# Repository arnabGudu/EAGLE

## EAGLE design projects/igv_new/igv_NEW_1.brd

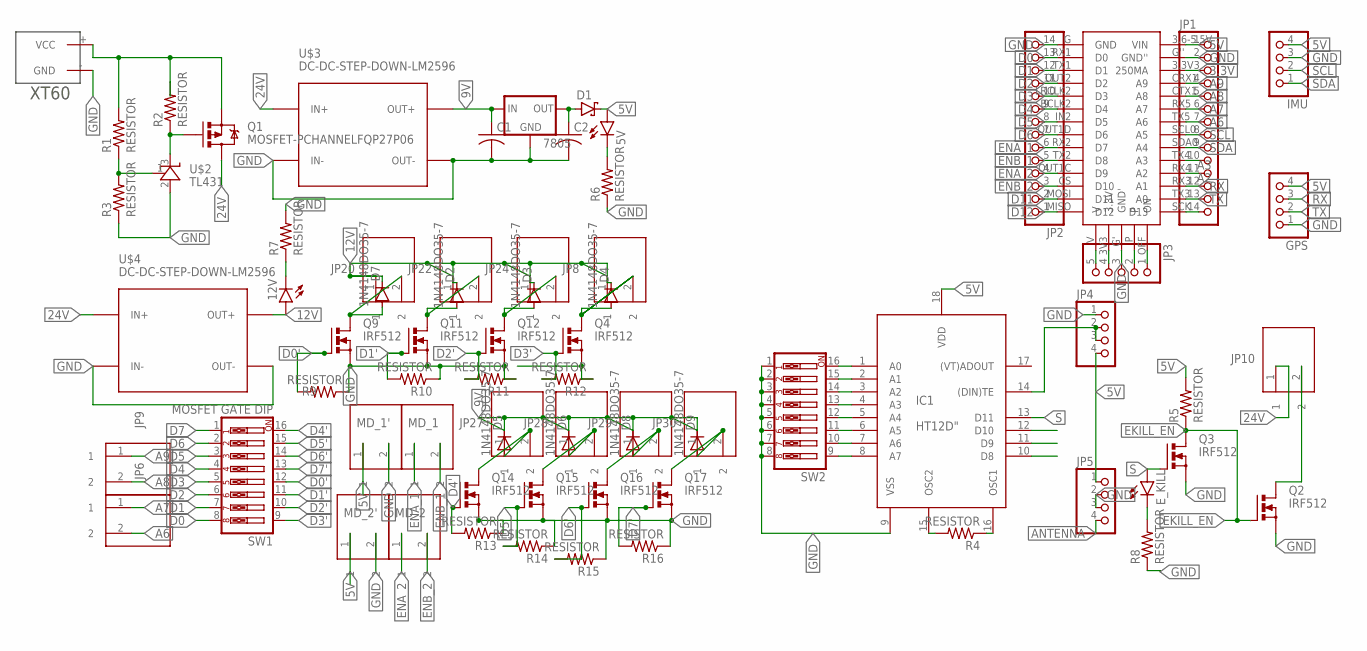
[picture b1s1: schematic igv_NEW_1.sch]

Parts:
5V, 12V: LED3MM
7805: 78XXS
C1, C2: C-US025-025X050; C025-025X050
D1: SCHOTTKY-DIODECB417-15; CB417-15
D2, D3, D4, D5, D6, D7, D8, D9: 1N4148DO35-7; DO35-7
E_KILL: LED3MM
GPS: ROTARY_ENCODER; 1X04
IC1: HT12D"; 18-DIP-A
IMU: ROTARY_ENCODER; 1X04
JP1, JP2: PINHD-1X14; 1X14
JP3: PINHD-1X5; 1X05
JP4, JP5: PINHD-1X4; 1X04
JP6, JP8, JP9, JP10, JP20, JP22, JP24, JP27, JP28, JP29, JP30: O/P_HEADER
MD_1, MD_1', MD_2, MD_2': O/P_HEADER
Q1: MOSFET-PCHANNELFQP27P06; TO220V
Q2, Q3, Q4, Q9, Q11, Q12, Q14, Q15, Q16, Q17: IRF512; TO220BV
R1, R2, R3, R4, R5, R6, R7, R8, R9, R10, R11, R12, R13, R14, R15, R16: RESISTOR; 0207/10
SW1: MOSFET GATE DIP; EDG-08
SW2: SW_DIP-8; EDG-08
U$1: TEENSY_4.0
U$2: TL431; TO-92
U$3, U$4: DC-DC-STEP-DOWN-LM2596
U$5: XT60

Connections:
3.3V: JP1.3, U$1.3.3V (250MA)
5V: 5V.A, D1.C, GPS.4, IC1.18 (VDD), IMU.4, JP1.1, JP4.4, JP5.1, MD_1'.1, MD_2'.1, R5.P$2 (2), U$1.3.6-5.5V (VIN)
9V: 7805.IN, C1.1, D5.C, D6.C, D8.C, D9.C, JP27.1, JP28.1, JP29.1, JP30.1, U$3.OUT+
12V: 12V.A, D2.C, D3.C, D4.C, D7.C, JP8.1, JP20.1, JP22.1, JP24.1, U$4.OUT+
24V: JP10.1, Q1.2 (D), U$3.IN+, U$4.IN+
A2: JP1.11, U$1.RX4 (A2)
A3: JP1.10, U$1.TX4 (A3)
A6: JP1.7, JP6.2, U$1.TX5 (A6)
A7: JP1.6, JP6.1, U$1.RX5 (A7)
A8: JP1.5, JP9.2, U$1.CTX1 (A8)
A9: JP1.4, JP9.1, U$1.CRX1 (A9)
ANTENNA: JP5.4
D0: JP2.13, SW1.8, U$1.RX1 (D0)
D0': Q9.G, R9.P$2 (2), SW1.12
D1: JP2.12, SW1.7, U$1.TX1 (D1)
D1': Q11.G, R10.P$2 (2), SW1.11
D2: JP2.11, SW1.6, U$1.OUT2 (D2)
D2': Q12.G, R11.P$2 (2), SW1.10
D3: JP2.10, SW1.5, U$1.LRCLK2 (D3)
D3': Q4.G, R12.P$2 (2), SW1.9
D4: JP2.9, SW1.4, U$1.BCLK2 (D4)
D4': Q14.G, R13.P$2 (2), SW1.16
D5: JP2.8, SW1.3, U$1.IN2 (D5)
D5': Q15.G, R14.P$2 (2), SW1.15
D6: JP2.7, SW1.2, U$1.OUT1D (D6)
D6': Q16.G, R15.P$2 (2), SW1.14
D7: SW1.1
D7': Q17.G, R16.P$2 (2), SW1.13
D11: JP2.2, U$1.MOSI (D11)
D12: JP2.1, U$1.MISO (D12)
EKILL_EN: Q2.G, Q3.D, R5.P$1 (1)
ENA_1: JP2.6, MD_1.1, U$1.RX2 (D7)
ENA_2: JP2.4, MD_2.1, U$1.OUT1C (D9)
ENB_1: JP2.5, MD_1.2, U$1.TX2 (D8)
ENB_2: JP2.3, MD_2.2, U$1.CS (D10)
GND: 7805.GND, C1.2, C2.2, GPS.1, IC1.9 (VSS), IMU.3, JP1.2, JP2.14, JP3.3, JP4.1, JP5.2, JP5.3, MD_1'.2, MD_2'.2, Q2.S, Q3.S, Q9.S, Q11.S, Q12.S, Q14.S, Q15.S, Q16.S, Q17.S, R3.P$1 (1), R6.P$1 (1), R7.P$2 (2), R8.P$1 (1), R9.P$1 (1), R10.P$1 (1), R11.P$1 (1), R13.P$1 (1), R14.P$1 (1), R15.P$1 (1), R16.P$1 (1), SW2.1, SW2.2, SW2.3, SW2.4, SW2.5, SW2.6, SW2.7, SW2.8, U$1.G (GND), U$1.G' (GND'), U$1.G'' (GND''), U$2.2 (A), U$3.IN-, U$3.OUT-, U$4.IN-, U$4.OUT-, U$5.- (GND)
GND1: Q4.S, R12.P$1 (1)
unnamed: Q1.3 (S), R1.P$2 (2), R2.P$2 (2), U$5.+ (VCC)
unnamed: D7.A, JP20.2, Q9.D
unnamed: IC1.15 (OSC2), R4.P$2 (2)
unnamed: R1.P$1 (1), R3.P$2 (2), U$2.1 (REF)
unnamed: 5V.K (C), R6.P$2 (2)
unnamed: E_KILL.K (C), R8.P$2 (2)
unnamed: JP10.2, Q2.D
unnamed: 12V.K (C), R7.P$1 (1)
unnamed: IC1.16 (OSC1), R4.P$1 (1)
unnamed: Q1.1 (G), R2.P$1 (1), U$2.3 (C)
unnamed: 7805.OUT, C2.1, D1.A
unnamed: D4.A, JP8.2
unnamed: JP1.14, U$1.SCK (D13)
unnamed: D2.A, JP22.2, Q11.D
unnamed: D3.A, JP24.2, Q12.D
unnamed: D5.A, JP27.2, Q14.D
unnamed: D6.A, JP28.2, Q15.D
unnamed: JP3.1, U$1.OFF (ON)
unnamed: JP3.2, U$1.P
unnamed: JP3.4, U$1.3V3 (3.3V)
unnamed: JP3.5, U$1.V
unnamed: IC1.8 (A7), SW2.9
unnamed: IC1.7 (A6), SW2.10
unnamed: IC1.6 (A5), SW2.11
unnamed: IC1.5 (A4), SW2.12
unnamed: IC1.4 (A3), SW2.13
unnamed: IC1.3 (A2), SW2.14
unnamed: IC1.2 (A1), SW2.15
unnamed: IC1.1 (A0), SW2.16
unnamed: IC1.14 ((DIN)TE), JP4.2, JP4.3
unnamed: D8.A, JP29.2, Q16.D
unnamed: D9.A, JP30.2, Q17.D
RX: GPS.3, JP1.12, U$1.RX3 (A1)
S: E_KILL.A, IC1.13 (D11), Q3.G
SCL: IMU.2, JP1.8, U$1.SCL0 (A5)
SDA: IMU.1, JP1.9, U$1.SDA0 (A4)
TX: GPS.2, JP1.13, U$1.TX3 (A0)

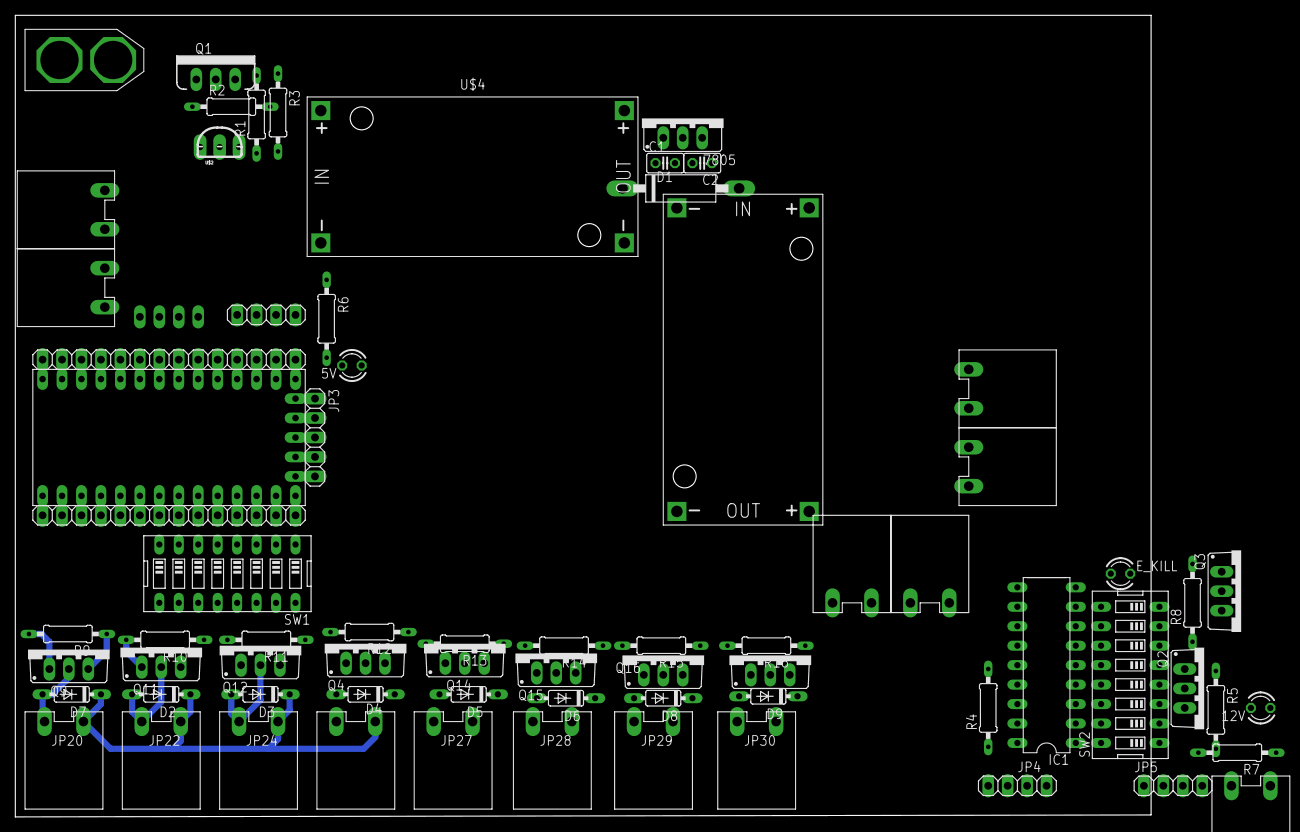
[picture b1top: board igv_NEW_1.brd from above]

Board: 2 copper layers, 148.3 x 104.6 mm, 72 parts (1 on the bottom side), 72 nets.

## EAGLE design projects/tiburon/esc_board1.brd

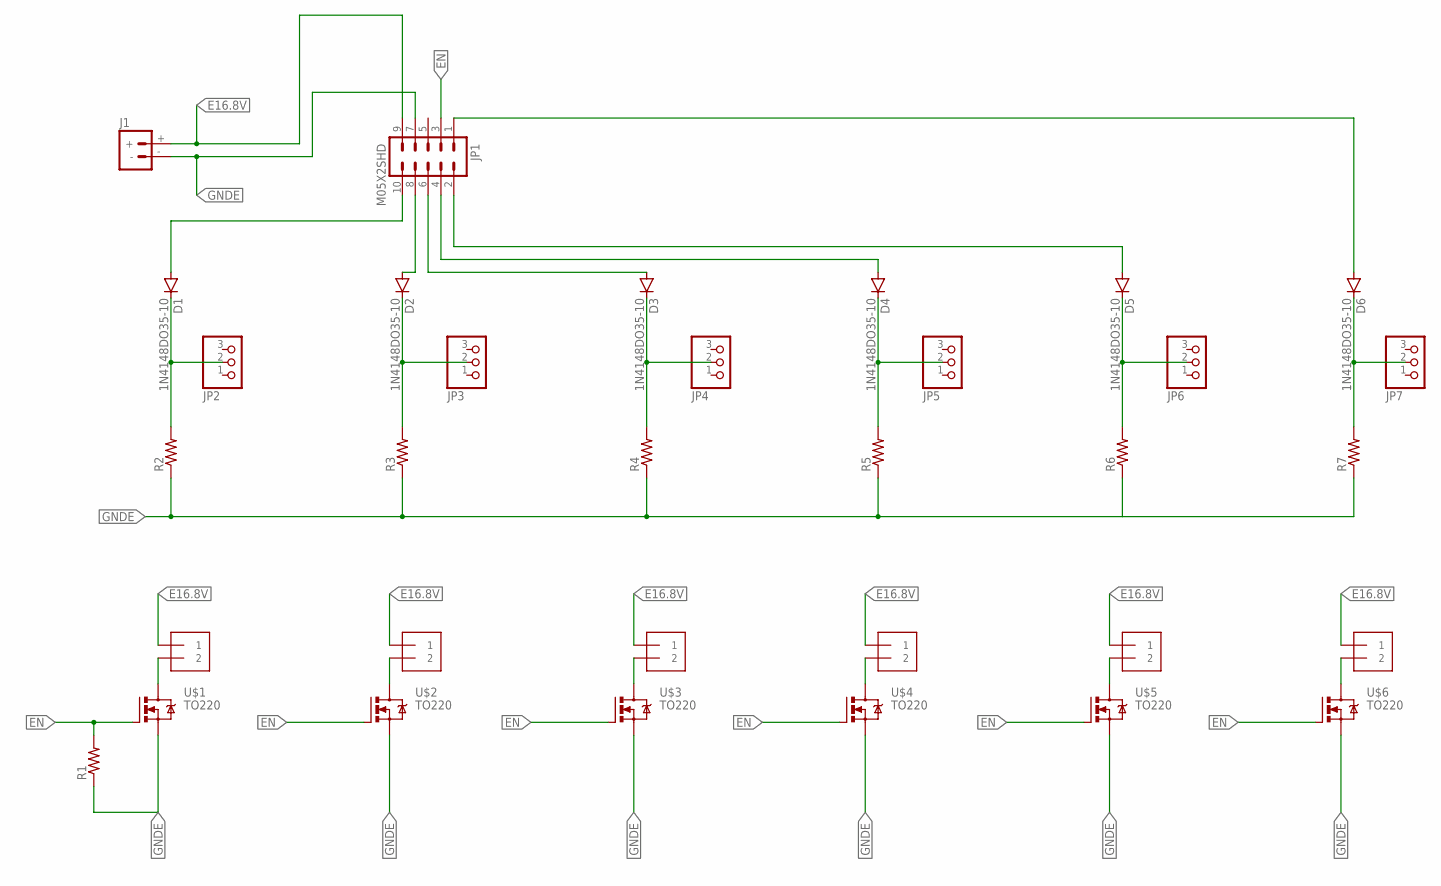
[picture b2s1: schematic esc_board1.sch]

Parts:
D1, D2, D3, D4, D5, D6: 1N4148DO35-10; DO35-10
J1: BATTERY_CONN_DEANS; DEANS
J7, J8, J9, J10, J11, J12: 1X2-3.5MM
JP1: M05X2SHD; 2X5-SHROUDED
JP2, JP3, JP4, JP5, JP6, JP7: PINHD-1X3; 1X03
R1, R2, R3, R4, R5, R6, R7: R-US_0204/7; 0204/7
U$1, U$2, U$3, U$4, U$5, U$6: TO220; IRF540

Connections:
E16.8V: J1.+, J7.1, J8.1, J9.1, J10.1, J11.1, J12.1, JP1.9
EN: JP1.3, R1.2, U$1.1 (G), U$2.1 (G), U$3.1 (G), U$4.1 (G), U$5.1 (G), U$6.1 (G)
GNDE: J1.-, JP1.7, R1.1, R2.1, R3.1, R4.1, R5.1, R6.1, R7.1, U$1.3 (S), U$2.3 (S), U$3.3 (S), U$4.3 (S), U$5.3 (S), U$6.3 (S)
unnamed: D1.A, JP1.10
unnamed: J7.2, U$1.2 (D)
unnamed: D1.C, JP2.2, R2.2
unnamed: D2.A, JP1.8
unnamed: J8.2, U$2.2 (D)
unnamed: D2.C, JP3.2, R3.2
unnamed: D3.A, JP1.6
unnamed: J9.2, U$3.2 (D)
unnamed: D3.C, JP4.2, R4.2
unnamed: D4.A, JP1.4
unnamed: J10.2, U$4.2 (D)
unnamed: D4.C, JP5.2, R5.2
unnamed: D5.A, JP1.2
unnamed: J11.2, U$5.2 (D)
unnamed: D5.C, JP6.2, R6.2
unnamed: D6.C, JP7.2, R7.2
unnamed: J12.2, U$6.2 (D)
unnamed: D6.A, JP1.1

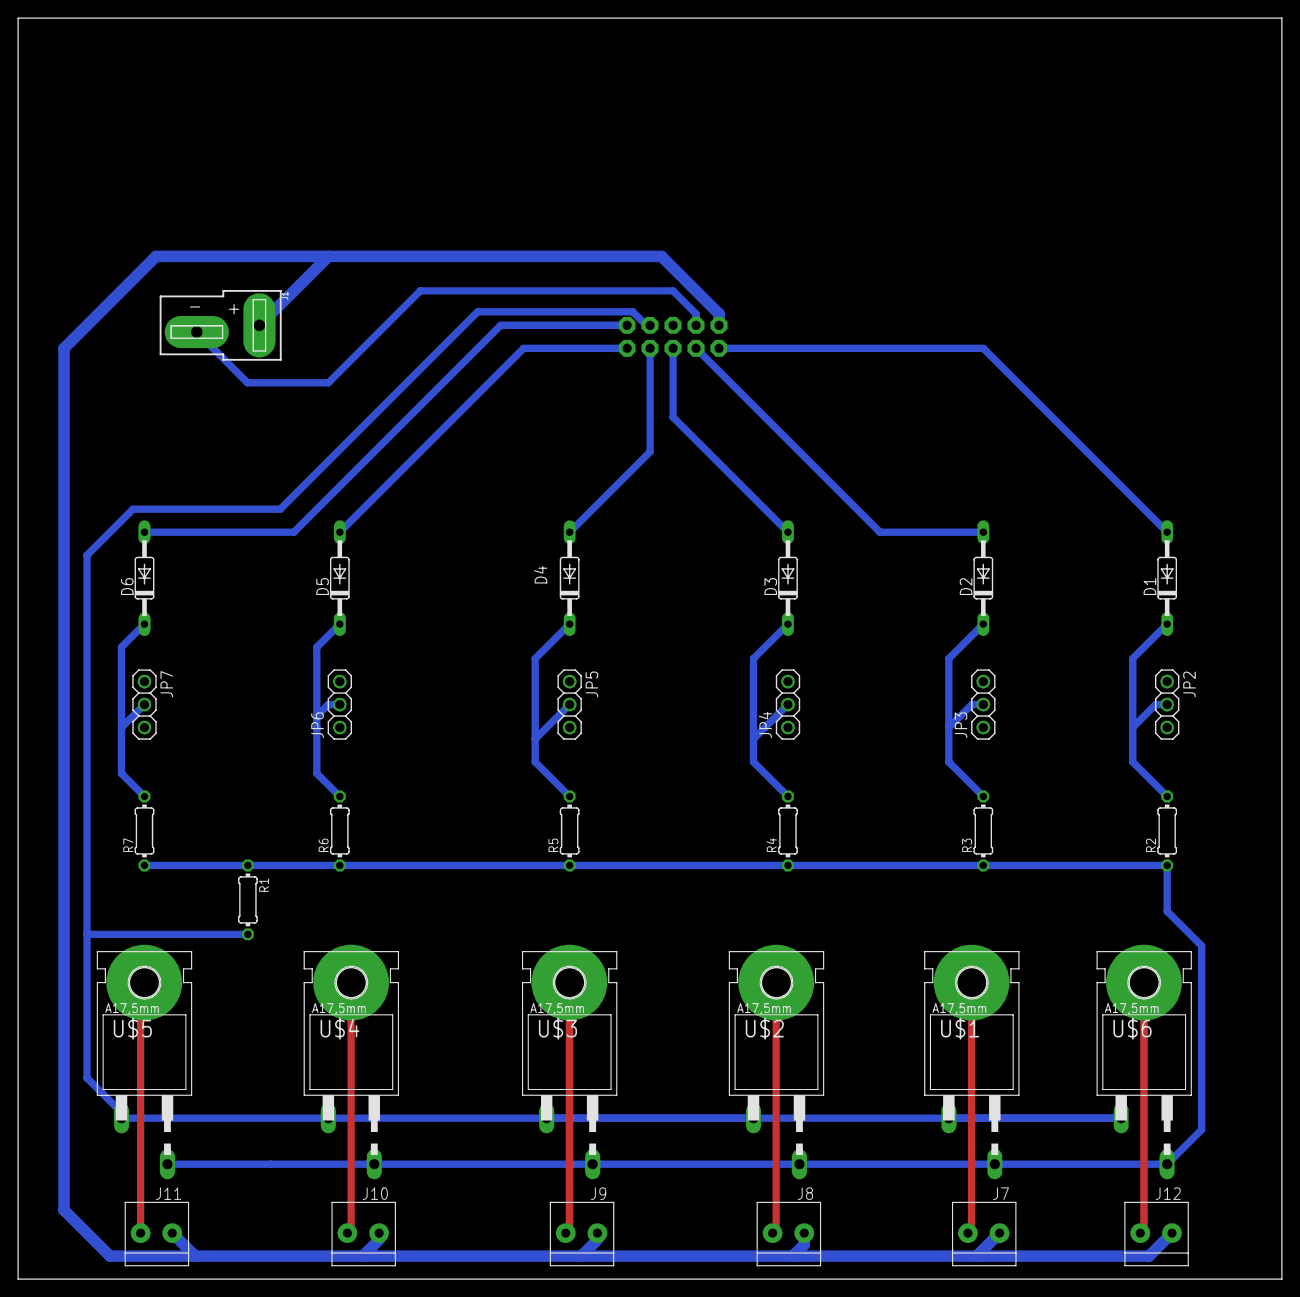
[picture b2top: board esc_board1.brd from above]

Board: 2 copper layers, 139.7 x 139.4 mm, 33 parts (1 on the bottom side), 21 nets.

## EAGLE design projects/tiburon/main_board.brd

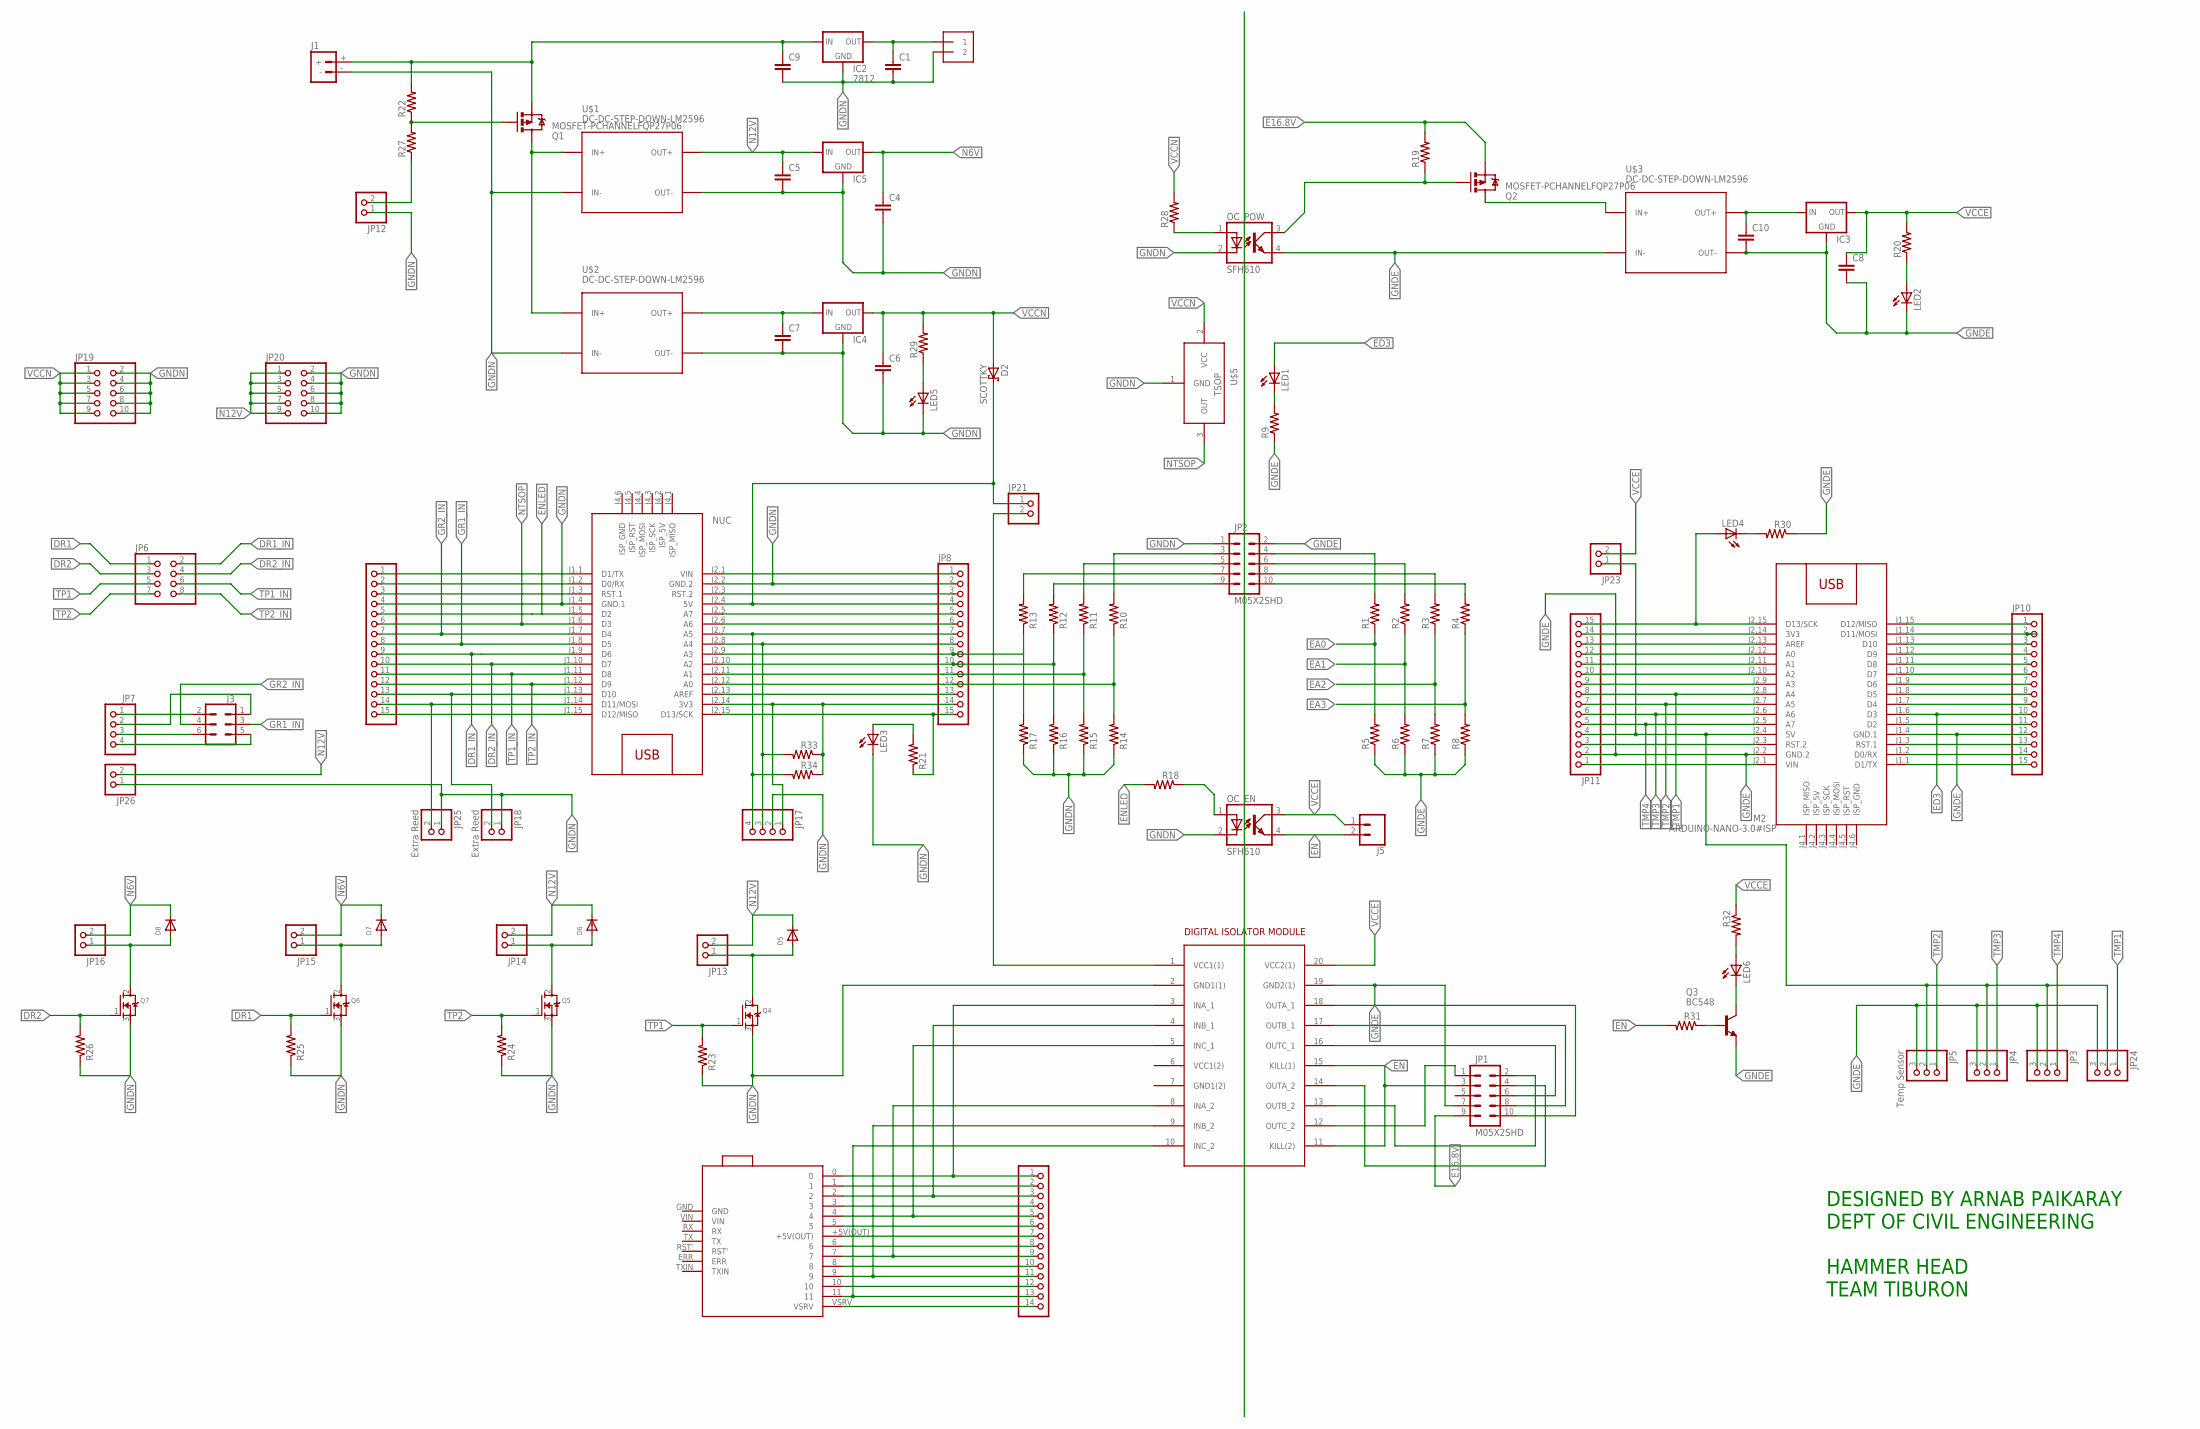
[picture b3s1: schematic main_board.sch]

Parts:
C1, C4, C5, C6, C7, C8, C9, C10: C-EU025-025X050; C025-025X050
D2: SCOTTKY; CB417-15
D5, D6, D7, D8: DIODEDO-1N4148; DO-1N4148
IC2: 7812; 78MXXS
IC3, IC4, IC5: 78XXS
J1: BATTERY_CONN_DEANS; DEANS
J3: CONN_03X2NO_SILK; 2X3-NS
J5: CONN_02LOCK_LONGPADS; 1X02_LOCK_LONGPADS
J6: 1X2-3.5MM
JP1, JP2: M05X2SHD; 2X5-SHROUDED
JP3, JP4, JP24: PINHD-1X3; 1X03
JP5: Temp Sensor; 1X03
JP6: PINHD-2X4; 2X04
JP7, JP17: PINHD-1X4; 1X04
JP8, JP9, JP10, JP11: PINHD-1X15; 1X15
JP12, JP13, JP14, JP15, JP16, JP21, JP23: PINHD-1X2; 1X02
JP18, JP25, JP26: Extra Reed; 1X02
JP19, JP20: PINHD-2X5; 2X05
JP22: PINHD-1X14; 1X14
LED1, LED2, LED3, LED4, LED5, LED6: LED3MM
M2: ARDUINO-NANO-3.0#ISP
NUC: ARDUINO-NANO-3.0#ISP
OC_EN: SFH610; DIL04
OC_POW: SFH610; DIL04
Q1, Q2: MOSFET-PCHANNELFQP27P06; TO220V
Q3: BC548; TO92-EBC
Q4, Q5, Q6, Q7: MOSFET-NGDS_TO220V; TO220V
R1, R2, R3, R4, R5, R6, R7, R8, R9, R10, R11, R12, R13, R14, R15, R16, R17, R18, R19, R20, R21, R22, R23, R24, R25, R26, R27, R28, R29, R30, R31, R32, R33, R34: R-US_0204/7; 0204/7
U$1, U$2, U$3: DC-DC-STEP-DOWN-LM2596
U$5: TSOP34X; TSOP3XXX
U$6: SERVO_CONTROLLER
U$7: DIGITAL_ISOLATOR; DIGITAL_ISOLATOR_MODULE

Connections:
DR1: JP6.1, Q6.1 (G), R25.2
DR1_IN: JP6.2, JP9.9, NUC.J1.9 (D6)
DR2: JP6.3, Q7.1 (G), R26.2
DR2_IN: JP6.4, JP9.10, NUC.J1.10 (D7)
E16.8V: JP1.9, Q2.3 (S), R19.2
EA0: JP11.12, M2.J2.12 (A0), R1.1, R5.2
EA1: JP11.11, M2.J2.11 (A1), R2.1, R6.2
EA2: JP11.10, M2.J2.10 (A2), R3.1, R7.2
EA3: JP11.9, M2.J2.9 (A3), R4.1, R8.2
ED3: JP10.10, LED1.A, M2.J1.6 (D3)
EN: J5.2, JP1.3, OC_EN.4 (EMIT), R31.2, U$7.11 (KILL(2)), U$7.15 (KILL(1))
ENLED: JP9.5, NUC.J1.5 (D2), R18.2
GNDE: C8.2, C10.2, IC3.GND, JP1.7, JP2.2, JP3.3, JP4.3, JP5.3, JP10.12, JP11.2, JP24.3, LED2.K (C), M2.J1.4 (GND.1), M2.J2.2 (GND.2), OC_POW.4 (EMIT), Q3.E, R5.1, R6.1, R7.1, R8.1, R9.1, R30.1, U$3.IN-, U$3.OUT-, U$7.19 (GND2(1))
GNDN: C1.2, C4.2, C5.2, C6.2, C7.2, C9.2, IC2.GND, IC4.GND, IC5.GND, J1.-, J6.2, JP2.1, JP8.2, JP9.4, JP12.1, JP17.2, JP18.1, JP19.2, JP19.4, JP19.6, JP19.8, JP19.10, JP20.2, JP20.4, JP20.6, JP20.8, JP20.10, JP25.1, JP26.1, LED3.K (C), LED5.K (C), NUC.J1.4 (GND.1), NUC.J2.2 (GND.2), OC_EN.2 (C), OC_POW.2 (C), Q4.3 (S), Q5.3 (S), Q6.3 (S), Q7.3 (S), R14.1, R15.1, R16.1, R17.1, R23.1, R24.1, R25.1, R26.1, U$1.IN-, U$1.OUT-, U$2.IN-, U$2.OUT-, U$5.1 (GND), U$7.2 (GND1(1))
GR1_IN: J3.3, JP9.8, NUC.J1.8 (D5)
GR2_IN: J3.4, JP9.7, NUC.J1.7 (D4)
N6V: C4.1, D7.C, D8.C, IC5.OUT, JP15.2, JP16.2
N12V: C5.1, D5.C, D6.C, IC5.IN, JP13.2, JP14.2, JP20.1, JP20.3, JP20.5, JP20.7, JP20.9, JP26.2, U$1.OUT+
unnamed: JP10.11, M2.J1.5 (D2)
unnamed: OC_EN.1 (A), R18.1
unnamed: JP9.1, NUC.J1.1 (D1/TX)
unnamed: JP9.2, NUC.J1.2 (D0/RX)
unnamed: JP9.3, NUC.J1.3 (RST.1)
unnamed: LED1.K (C), R9.2
unnamed: JP2.4, R1.2
unnamed: JP2.6, R2.2
unnamed: JP2.8, R3.2
unnamed: JP2.10, R4.2
unnamed: JP8.7, JP17.4, NUC.J2.7 (A5), R34.2
unnamed: JP8.8, JP17.3, NUC.J2.8 (A4), R33.2
unnamed: LED3.A, R21.2
unnamed: JP2.3, R10.2
unnamed: JP2.5, R11.2
unnamed: LED4.K (C), R30.2
unnamed: JP2.9, R12.2
unnamed: JP2.7, R13.2
unnamed: JP22.12, U$6.10
unnamed: OC_POW.3 (COL), Q2.1 (G), R19.1
unnamed: JP22.10, U$6.8
unnamed: C10.1, IC3.IN, U$3.OUT+
unnamed: JP22.3, U$6.2, U$7.4 (INB_1)
unnamed: Q2.2 (D), U$3.IN+
unnamed: LED2.A, R20.1
unnamed: JP8.14, JP17.1, NUC.J2.14 (3V3), R33.1, R34.1
unnamed: D2.C, JP8.4, JP21.1, NUC.J2.4 (5V)
unnamed: JP3.2, JP4.2, JP5.2, JP11.4, JP23.1, JP24.2, M2.J2.4 (5V)
unnamed: JP8.10, NUC.J2.10 (A2), R12.1, R16.2
unnamed: Q3.B, R31.1
unnamed: JP22.8, U$6.6
unnamed: JP1.1, U$7.12 (OUTC_2)
unnamed: JP1.2, U$7.13 (OUTB_2)
unnamed: JP22.13, U$6.11, U$7.10 (INC_2)
unnamed: C9.1, IC2.IN, J1.+, Q1.3 (S), R22.2
unnamed: C1.1, IC2.OUT, J6.1
unnamed: JP22.2, U$6.1
unnamed: JP1.4, U$7.14 (OUTA_2)
unnamed: JP1.6, U$7.16 (OUTC_1)
unnamed: JP1.8, U$7.17 (OUTB_1)
unnamed: JP11.1, M2.J2.1 (VIN)
unnamed: JP1.10, U$7.18 (OUTA_1)
unnamed: JP9.13, JP18.2, NUC.J1.13 (D10)
unnamed: JP9.14, JP25.2, NUC.J1.14 (D11/MOSI)
unnamed: JP8.13, NUC.J2.13 (AREF)
unnamed: JP9.15, NUC.J1.15 (D12/MISO)
unnamed: JP22.11, U$6.9, U$7.9 (INB_2)
unnamed: J3.6, JP7.3
unnamed: J3.2, JP7.1
unnamed: J3.1, JP7.2
unnamed: J3.5, JP7.4
unnamed: JP8.1, NUC.J2.1 (VIN)
unnamed: JP8.9, NUC.J2.9 (A3), R13.1, R17.2
unnamed: JP8.3, NUC.J2.3 (RST.2)
unnamed: JP21.2, U$7.1 (VCC1(1))
unnamed: JP22.4, U$6.3
unnamed: JP22.9, U$6.7, U$7.8 (INA_2)
unnamed: JP8.15, NUC.J2.15 (D13/SCK), R21.1
unnamed: JP22.6, U$6.5
unnamed: JP22.7, U$6.+5V(OUT)
unnamed: JP22.5, U$6.4, U$7.5 (INC_1)
unnamed: Q1.1 (G), R22.1, R27.2
unnamed: JP22.1, U$6.0, U$7.3 (INA_1)
unnamed: JP10.1, M2.J1.15 (D12/MISO)
unnamed: JP10.2, M2.J1.14 (D11/MOSI)
unnamed: JP10.3, M2.J1.13 (D10)
unnamed: JP10.4, M2.J1.12 (D9)
unnamed: JP10.5, M2.J1.11 (D8)
unnamed: JP10.6, M2.J1.10 (D7)
unnamed: JP10.7, M2.J1.9 (D6)
unnamed: JP10.8, M2.J1.8 (D5)
unnamed: JP10.9, M2.J1.7 (D4)
unnamed: JP22.14, U$6.VSRV
unnamed: JP10.13, M2.J1.3 (RST.1)
unnamed: JP10.14, M2.J1.2 (D0/RX)
unnamed: JP10.15, M2.J1.1 (D1/TX)
unnamed: JP11.15, LED4.A, M2.J2.15 (D13/SCK)
unnamed: JP11.14, M2.J2.14 (3V3)
unnamed: JP11.13, M2.J2.13 (AREF)
unnamed: JP11.3, M2.J2.3 (RST.2)
unnamed: D5.A, JP13.1, Q4.2 (D)
unnamed: D6.A, JP14.1, Q5.2 (D)
unnamed: JP12.2, R27.1
unnamed: D7.A, JP15.1, Q6.2 (D)
unnamed: D8.A, JP16.1, Q7.2 (D)
unnamed: C7.1, IC4.IN, U$2.OUT+
unnamed: OC_POW.1 (A), R28.1
unnamed: Q1.2 (D), U$1.IN+, U$2.IN+
unnamed: LED5.A, R29.1
unnamed: LED6.K (C), Q3.C
unnamed: LED6.A, R32.2
NA0: JP8.5, NUC.J2.5 (A7)
NA1: JP8.6, NUC.J2.6 (A6)
NA2: JP8.11, NUC.J2.11 (A1), R11.1, R15.2
NA3: JP8.12, NUC.J2.12 (A0), R10.1, R14.2
NTSOP: JP9.6, NUC.J1.6 (D3), U$5.3 (OUT)
TMP1: JP11.8, JP24.1, M2.J2.8 (A4)
TMP2: JP5.1, JP11.7, M2.J2.7 (A5)
TMP3: JP4.1, JP11.6, M2.J2.6 (A6)
TMP4: JP3.1, JP11.5, M2.J2.5 (A7)
TP1: JP6.5, Q4.1 (G), R23.2
TP1_IN: JP6.6, JP9.11, NUC.J1.11 (D8)
TP2: JP6.7, Q5.1 (G), R24.2
TP2_IN: JP6.8, JP9.12, NUC.J1.12 (D9)
VCCE: C8.1, IC3.OUT, J5.1, JP23.2, OC_EN.3 (COL), R20.2, R32.1, U$7.20 (VCC2(1))
VCCN: C6.1, D2.A, IC4.OUT, JP19.1, JP19.3, JP19.5, JP19.7, JP19.9, R28.2, R29.2, U$5.2 (VCC)

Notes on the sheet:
DESIGNED BY ARNAB PAIKARAY DEPT OF CIVIL ENGINEERING HAMMER HEAD TEAM TIBURON

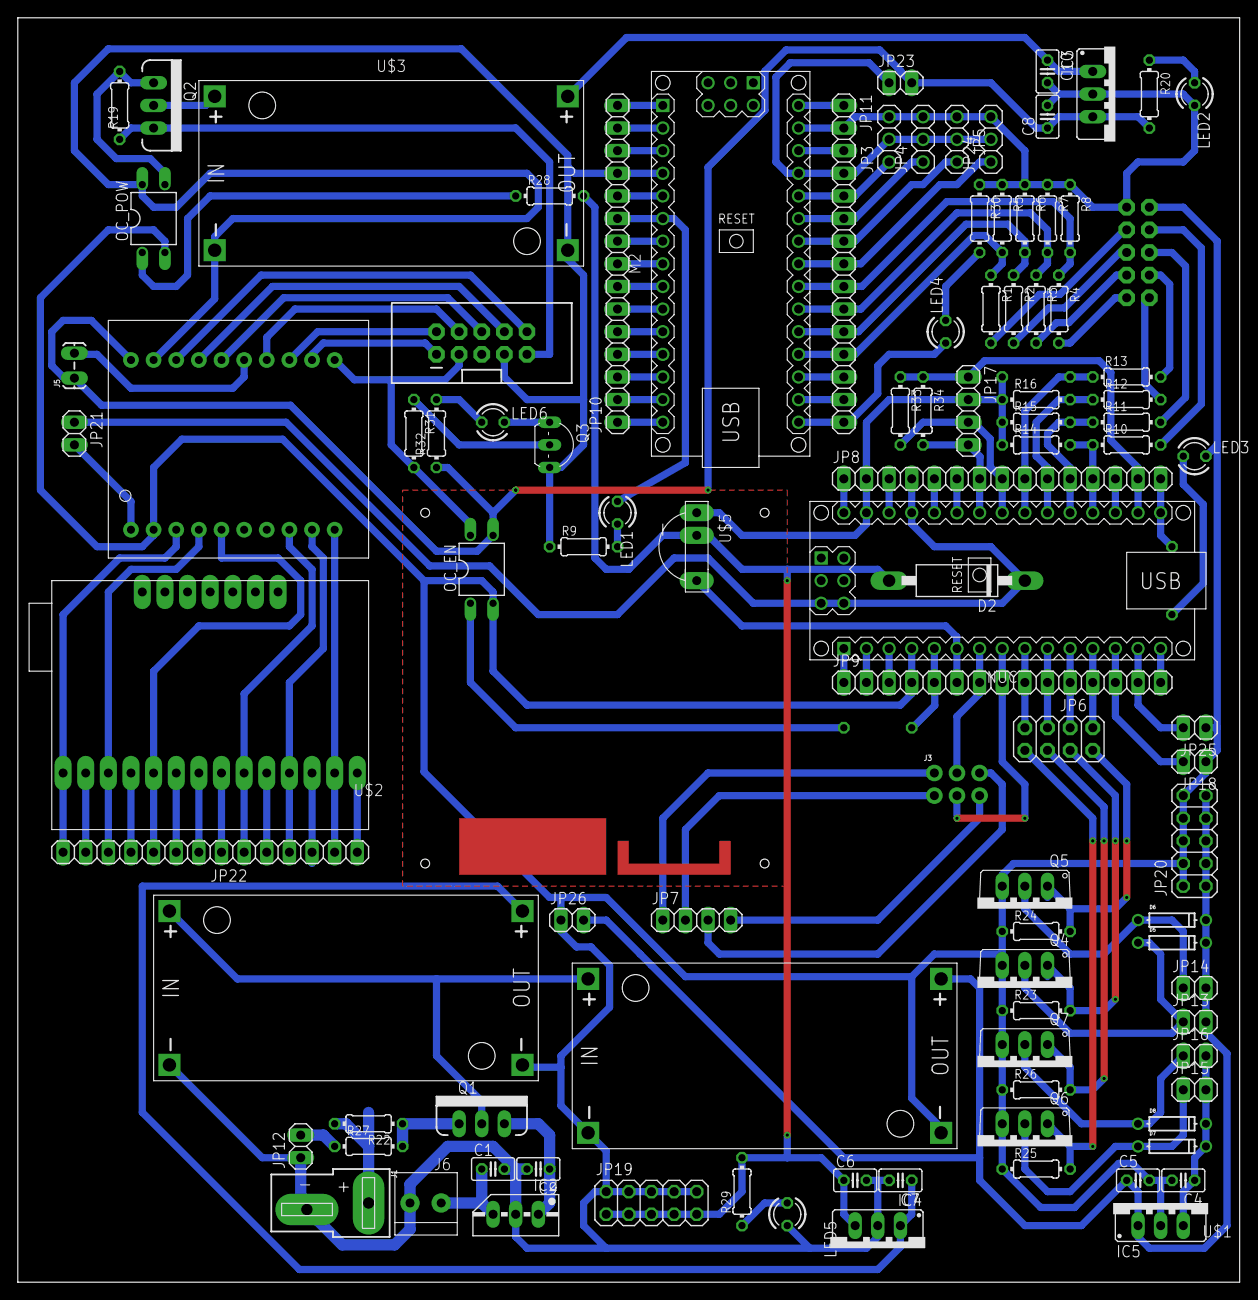
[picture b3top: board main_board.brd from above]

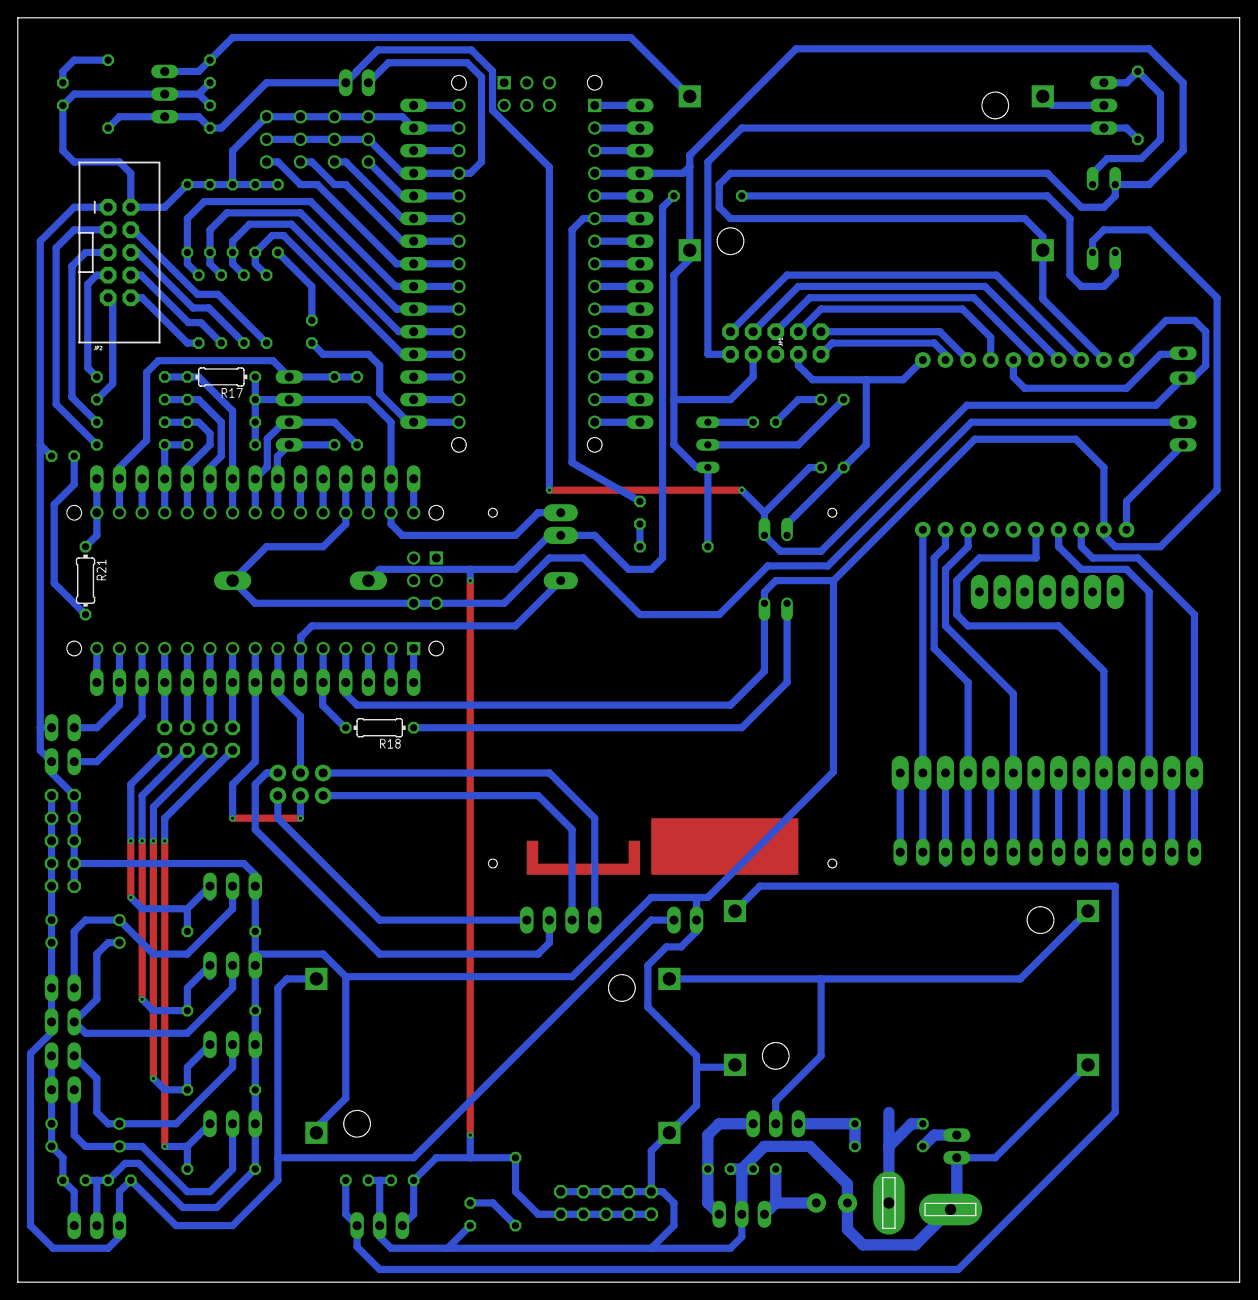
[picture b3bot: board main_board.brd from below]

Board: 2 copper layers, 137.1 x 141.9 mm, 104 parts (4 on the bottom side), 124 nets.

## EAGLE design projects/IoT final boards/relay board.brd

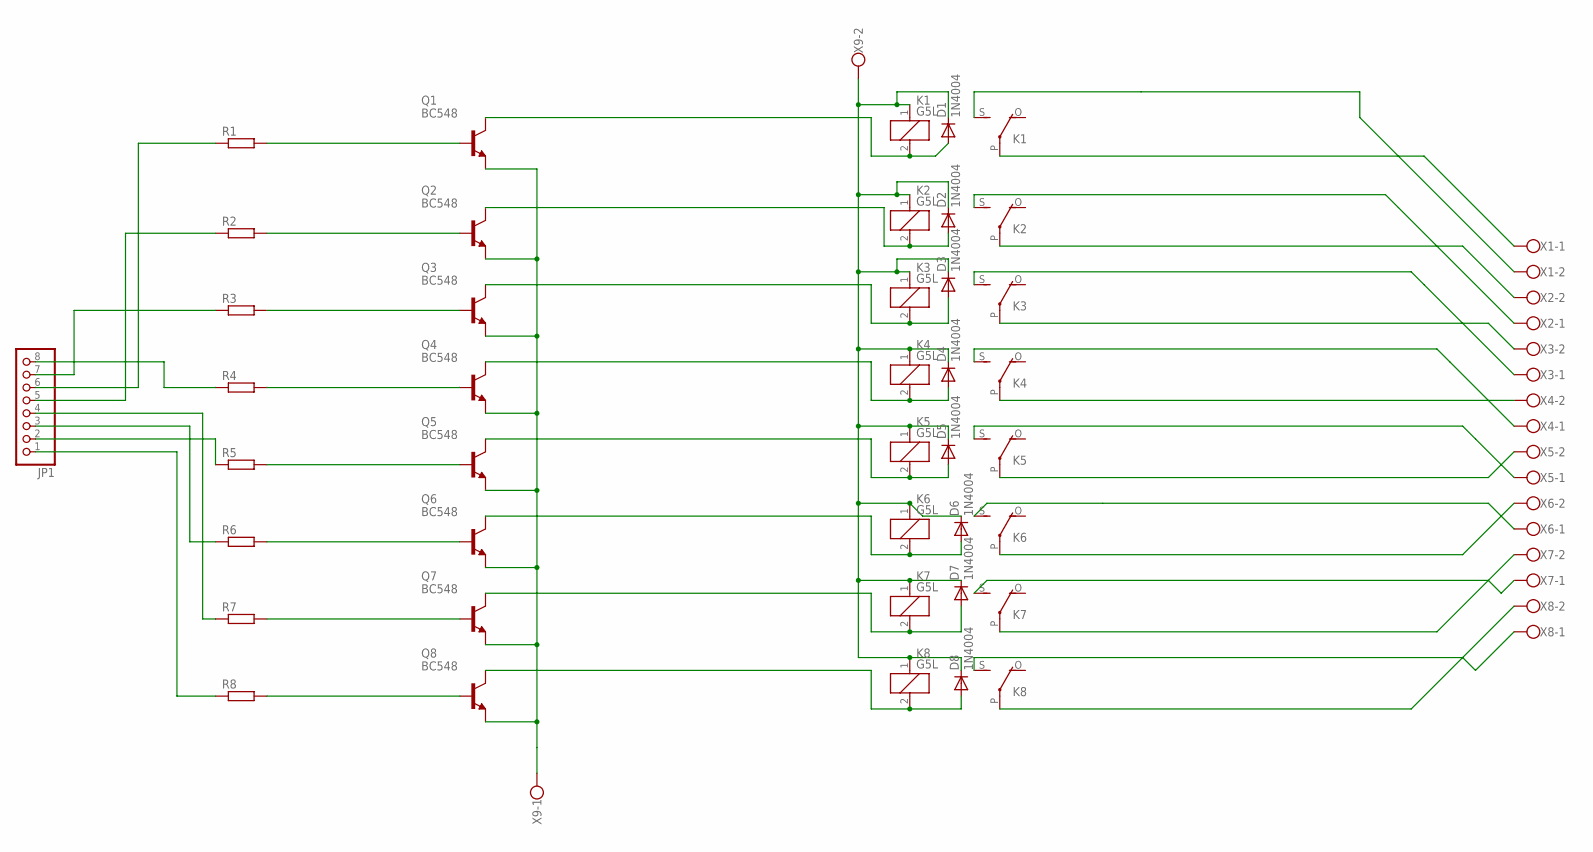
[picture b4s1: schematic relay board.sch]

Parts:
D1, D2, D3, D4, D5, D6, D7, D8: 1N4004; DO41-10
JP1: PINHD-1X8; 1X08
K1, K2, K3, K4, K5, K6, K7, K8: G5L; G5LE
Q1, Q2, Q3, Q4, Q5, Q6, Q7, Q8: BC548; TO92-EBC
R1, R2, R3, R4, R5, R6, R7, R8: RCL_R-EU_0207/10; RCL_0207/10
X1, X2, X3, X4, X5, X6, X7, X8, X9: W237-102

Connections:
12V: D1.C, D2.C, D3.C, D4.C, D5.C, D6.C, D7.C, D8.C, K1.1, K2.1, K3.1, K4.1, K5.1, K6.1, K7.1, K8.1, X9.2
GND: Q1.E, Q2.E, Q3.E, Q4.E, Q5.E, Q6.E, Q7.E, Q8.E, X9.1
unnamed: JP1.2, R5.1
unnamed: D1.A, K1.2, Q1.C
unnamed: D2.A, K2.2, Q2.C
unnamed: D3.A, K3.2, Q3.C
unnamed: D4.A, K4.2, Q4.C
unnamed: D5.A, K5.2, Q5.C
unnamed: D6.A, K6.2, Q6.C
unnamed: D7.A, K7.2, Q7.C
unnamed: D8.A, K8.2, Q8.C
unnamed: K1.P, X1.1
unnamed: K2.P, X2.2
unnamed: K3.P, X3.2
unnamed: K4.P, X4.2
unnamed: K5.P, X5.2
unnamed: K6.P, X6.2
unnamed: K7.P, X7.2
unnamed: Q1.B, R1.2
unnamed: Q2.B, R2.2
unnamed: Q3.B, R3.2
unnamed: Q4.B, R4.2
unnamed: Q5.B, R5.2
unnamed: Q6.B, R6.2
unnamed: Q7.B, R7.2
unnamed: Q8.B, R8.2
unnamed: JP1.5, R2.1
unnamed: JP1.6, R1.1
unnamed: JP1.7, R3.1
unnamed: JP1.8, R4.1
unnamed: JP1.4, R7.1
unnamed: JP1.3, R6.1
unnamed: JP1.1, R8.1
unnamed: K8.P, X8.2
unnamed: K1.S, X1.2
unnamed: K2.S, X2.1
unnamed: K3.S, X3.1
unnamed: K4.S, X4.1
unnamed: K5.S, X5.1
unnamed: K7.S, X7.1
unnamed: K8.S, X8.1
unnamed: K6.S, X6.1

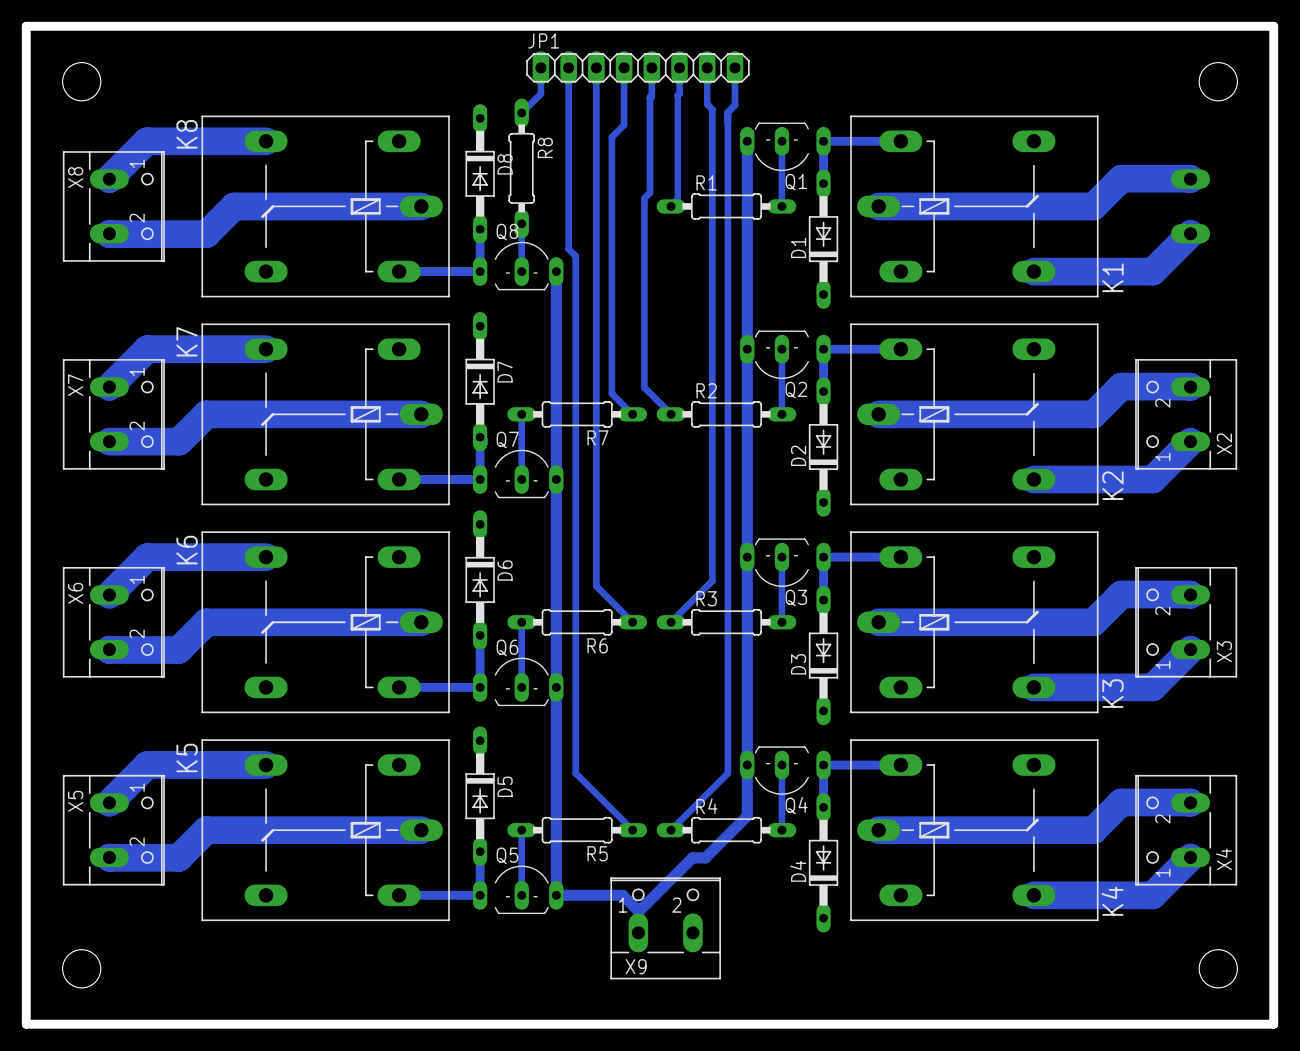
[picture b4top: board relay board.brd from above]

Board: 2 copper layers, 114.3 x 91.4 mm, 42 parts (1 on the bottom side), 42 nets.

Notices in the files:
parts and their libraries:
microbuilder: This work is placed in the public domain, and may be freely used for commercial and non-commercial work with the following conditions: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
op-amp: Copyright (C) 2006 by Bob Starr
